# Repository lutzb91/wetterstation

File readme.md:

# Wetterstation

## Komponenten

* Regensensor
* Windgeschwindigkeit
* Windrichtung
* Temperatur, etc (BME280)
* Solarzelle Intensität
* Kompass (GY-511)
* Laderegler (MCP-73871)
* Arduino
* Solarzelle Versorgung

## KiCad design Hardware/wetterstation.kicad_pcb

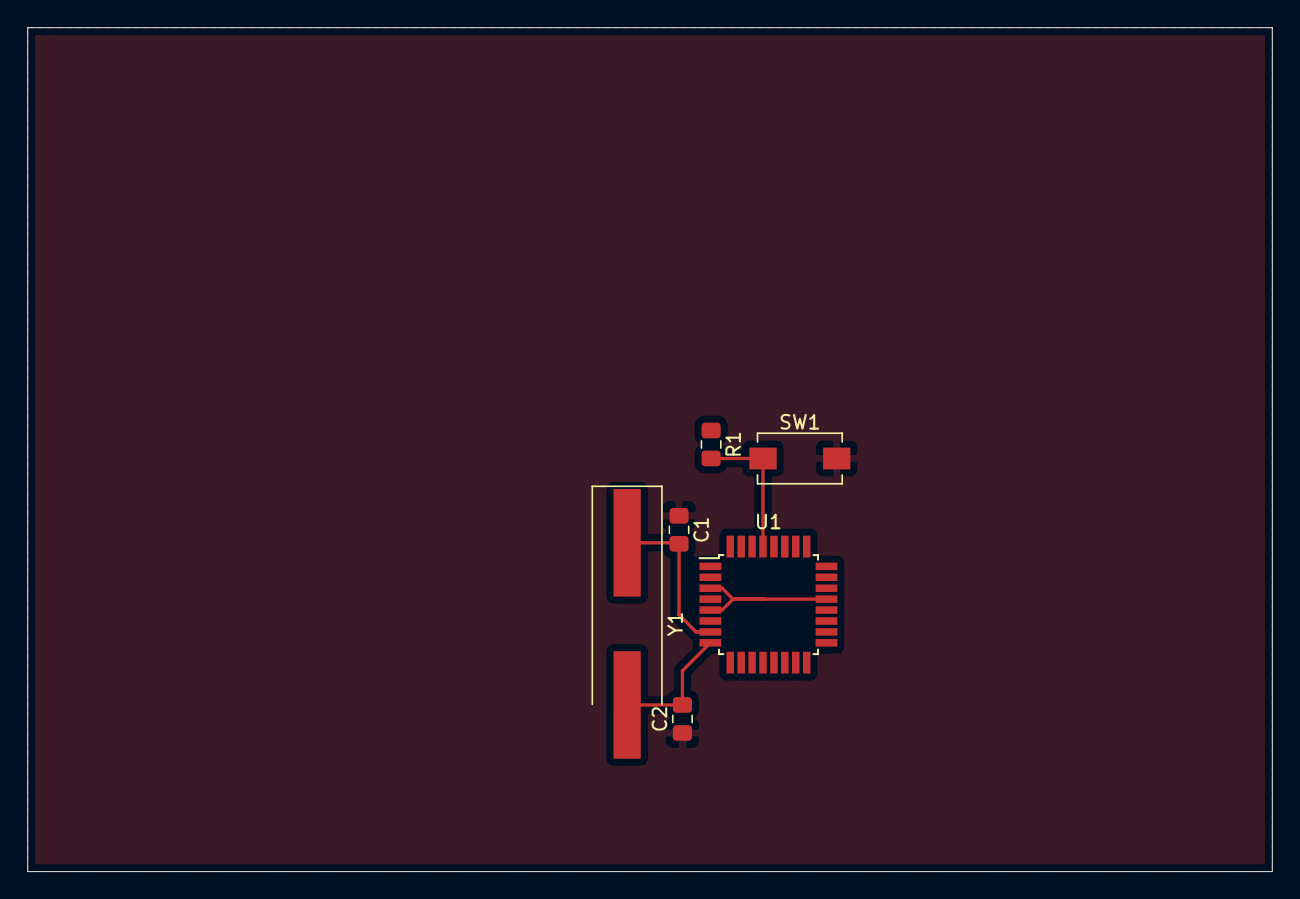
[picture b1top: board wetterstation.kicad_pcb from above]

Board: 2 copper layers, 91.2 x 61.8 mm, 6 parts (0 on the bottom side), 6 nets.

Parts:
C1, C2: 22pF; C_0805_2012Metric_Pad1.15x1.40mm_HandSolder
R1: 10k; R_0805_2012Metric_Pad1.15x1.40mm_HandSolder
SW1: Reset; SW_SPST_EVQPE1
U1: ATmega328P-AU; TQFP-32_7x7mm_P0.8mm
Y1: 8MHz; Crystal_SMD_HC49-SD_HandSoldering

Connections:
GND: C1.1, C2.1, SW1.2
unnamed: C1.2, U1.7, Y1.1
unnamed: C2.2, U1.8, Y1.2
unnamed: R1.2, SW1.1, U1.29
unnamed: U1.4, U1.6
unnamed: U1.3, U1.5, U1.21

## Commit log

2020-12-16 Kommentare
2020-12-16 aufraeumen
2020-12-16 aufraeumen #2
2020-12-16 Windrichtungsensor hinzugefuegt
2020-12-17 Test.txt hinzugefuegt
2020-12-17 Arduino in Schaltplan aufgebaut
2020-12-29 Regensensor ausimplementiert
